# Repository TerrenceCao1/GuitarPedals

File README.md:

# Digital Guitar Pedals

A modular digital guitar pedal platform built on the STM32F103C8T6 microcontroller. The goal is a single hardware enclosure that can be reflashed to produce different effects.

---

## Effects Firmware

| Effect | Status |
|---|---|
| Bypass (clean passthrough) | Software Tested |
| Boost | Planned |
| Overdrive / Distortion | Planned |
| Delay | Planned |
| Chorus | Planned |
| Reverb | Planned |
| Tremolo | Planned |
| Tuner | Planned |
| Looper | Planned |

---

## Hardware

### Signal Chain

```
Guitar → 1/4" input jack → input protection → op-amp buffer → ADC (PCM1802)
                                                                      ↓
Amp    ← 1/4" output jack ←   output cap    ← DAC (PCM5102A) ← STM32 via I2S
```

### Power

Powered via USB through the STM32 Blue Pill's onboard regulator. No external PSU needed.

| Rail | Source | Powers |
|---|---|---|
| 3.3V | Blue Pill `3V3` pin | STM32, PCM1802, PCM5102A |
| 5V | Blue Pill `5V` pin | MCP6002 op-amp |

### Components

| Component | Part | Status | Link |
|---|---|---|---|
| Microcontroller | STM32F103C8T6 (Blue Pill) | Have | — |
| ADC | PCM1802 | Ordered | [Amazon](https://www.amazon.com/PCM1808-Single-Ended-Analog-Input-Decoder-Amplifier/dp/B0D9LNGBD1) |
| DAC | PCM5102A breakout | Ordered | [Amazon](https://www.amazon.com/ACEIRMC-Lossless-Digital-Converter-Raspberry/dp/B08YNJGSN4) |
| Op-amp | MCP6002 (rail-to-rail, 3.3V/5V) | Ordered | [Amazon](https://www.amazon.com/MICROCHIP-MCP6002-I-OP-AMP-DIP-8-pieces/dp/B00LPJXQJW) |
| Input/output jacks | GLS 1/4" female panel jacks × 2 | Ordered | [Amazon](https://www.amazon.com/GLS-Audio-Jacks-Female-Panel/dp/B00CMXRLXM) |
| Input protection | 1MΩ resistor + 10nF capacitor | Ordered | [Resistors](https://www.amazon.com/ALLECIN-8W-Resistor-Film-Assortment/dp/B0BTP6WYH1) / [Caps](https://www.amazon.com/Multilayer-Monolithic-Capacitor-Assortment-Electronics/dp/B0D2GVNDHY) |
| Decoupling caps | 100nF ceramic × 8, 10µF electrolytic × 2 | Needed | — |
| Breadboard + jumper wires | Full-size 830-tie | Have | — |

---

## Roadmap

- [ ] Breadboard MVP — get audio passing through STM32 via I2S
- [ ] Implement and test simulations (pure software on computer)
- [ ] Test effects on firmware
- [ ] Wire potentiometers for live parameter control
- [ ] Design schematic and PCB
- [ ] Design and fabricate enclosure

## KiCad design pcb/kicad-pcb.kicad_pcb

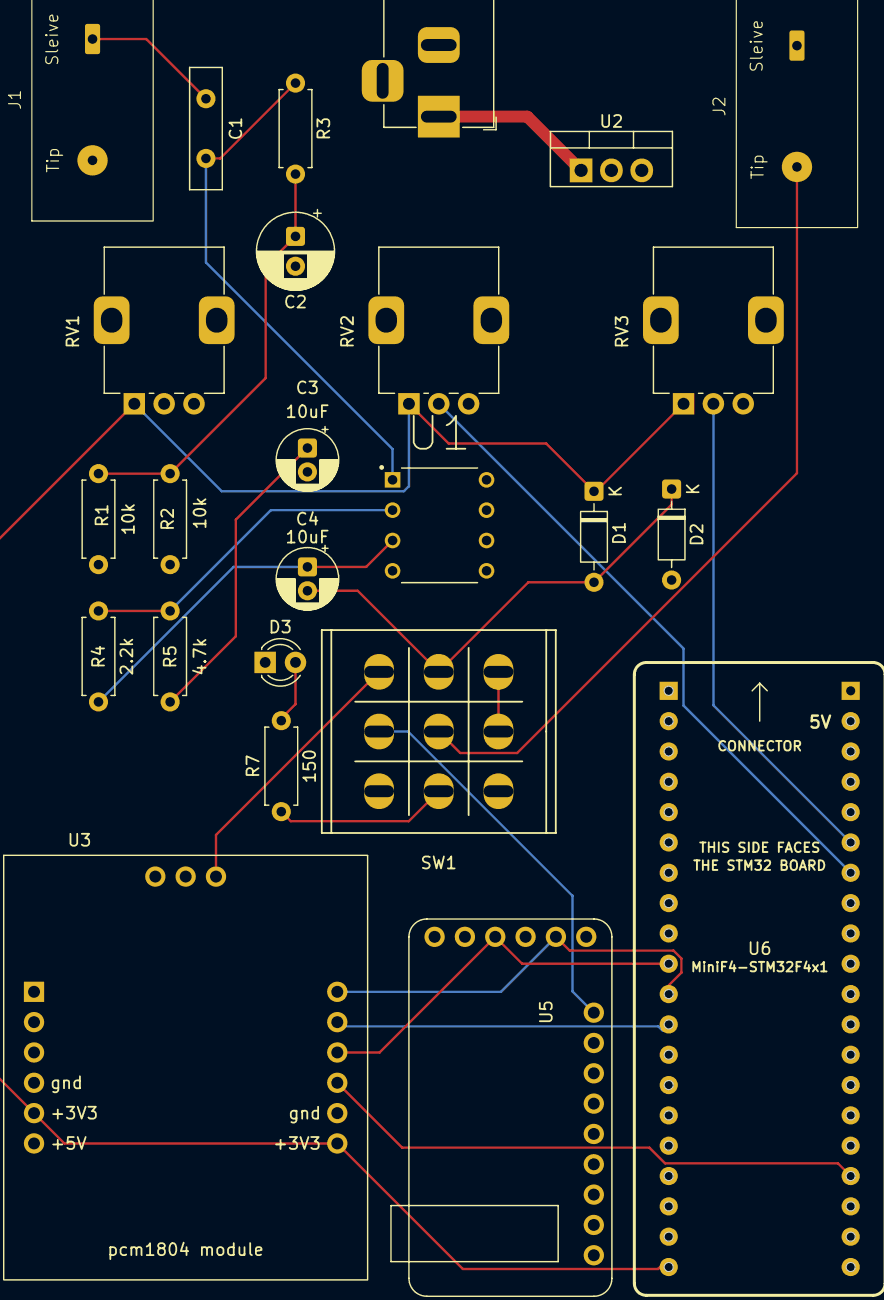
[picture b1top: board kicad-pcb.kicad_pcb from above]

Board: 4 copper layers, 25 parts (0 on the bottom side), 25 nets.

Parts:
C1: 0.1uF; C_Disc_D10.0mm_W2.5mm_P5.00mm
C2: 47uF; CP_Radial_D6.3mm_P2.50mm
C3, C4: 10uF; CP_Radial_D5.0mm_P2.00mm
D1, D2: BAT41; D_DO-35_SOD27_P7.62mm_Horizontal
D3: LED; LED_D3.0mm
J1: InputJack; AudioJack
J2: OutputJack; AudioJack
J3: Power Jack; BarrelJack_Horizontal
R1, R2: 10k; R_Axial_DIN0207_L6.3mm_D2.5mm_P7.62mm_Horizontal
R3: 1M; R_Axial_DIN0207_L6.3mm_D2.5mm_P7.62mm_Horizontal
R4: 2.2k; R_Axial_DIN0207_L6.3mm_D2.5mm_P7.62mm_Horizontal
R5: 4.7k; R_Axial_DIN0207_L6.3mm_D2.5mm_P7.62mm_Horizontal
R7: 150; R_Axial_DIN0207_L6.3mm_D2.5mm_P7.62mm_Horizontal
RV1: Knob1; Potentiometer_Alps_RK09K_Single_Vertical
RV2: Knob2; Potentiometer_Alps_RK09K_Single_Vertical
RV3: Knob3; Potentiometer_Alps_RK09K_Single_Vertical
SW1: Switches_Stomp_Switch_3PDT
U1: DIP787W46P254L927H533Q8
U2: LM7805_TO220; TO-220-3_Vertical
U3: pcm_adc
U5: GY-PCM5102
U6: Mini_F4X1_STM32

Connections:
+3.3V: D1.1 (K), RV1.1, RV2.1, RV3.1, U3.8 (3.3V), U3.15 (3.3V), U6.20 (3V3), U6.23 (3V3)
+5V: R1.1, SW1.7 (A), U1.4 (V+), U2.3 (VO), U3.9 (5V), U5.6 (VIN), U6.18 (5V), U6.21 (5V)
+9V: J3.1, U2.1 (VI)
GND: C2.2, C3.2, D2.2 (A), D3.1 (K), J1.T, J2.S, J3.2, R2.2, RV1.3, RV2.3, RV3.3, SW1.9 (C), U2.2 (GND), U3.2 (GND), U3.4 (FMT), U3.5 (MD1), U3.6 (MD0), U3.7 (GND), U3.14 (GND), U5.1 (SCK), U5.5 (GND), U5.12 (G), U5.14 (G), U6.19 (GND), U6.22 (GND)
unnamed: C1.1, J1.S
unnamed: C2.1, R1.2, R2.1, R3.2
unnamed: C3.1, R5.2
unnamed: C4.1, R4.1, U1.3
unnamed: C4.2, D1.2 (A), D2.1 (K), SW1.2 (B)
unnamed: D3.2 (A), R7.2
unnamed: SW1.1 (A), U3.3 (LIN)
unnamed: SW1.3 (C), SW1.6 (C)
unnamed: SW1.4 (A), U5.15 (L)
unnamed: J2.T, SW1.5 (B)
unnamed: R7.1, SW1.8 (B)
unnamed: C1.2, R3.1, U1.1 (+)
unnamed: R4.2, R5.1, U1.2 (-)
unnamed: U3.10 (BCK), U5.2 (BCK), U6.11 (B3)
unnamed: U3.12 (LRC), U5.4 (LCK), U6.10 (A15)
unnamed: U3.11 (OUT), U6.12 (B4)
unnamed: U3.13 (SCK), U6.24 (B10)
unnamed: U5.3 (DIN), U6.13 (B5)
unnamed: RV3.2, U6.35 (A0)
unnamed: RV2.2, U6.34 (A1)
unnamed: RV1.2, U6.32 (A3)

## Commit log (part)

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2026-06-03 initial commit, with AudioFrame data class
2026-06-03 added info/scope to the project
2026-06-08 reformatted tests and wrote distortion tests
2026-06-08 finished normalize and assignment operator for AudioFrame
2026-06-13 distort function tests
2026-06-13 readme updates
2026-06-20 cmake includes tests
2026-06-20 new access functions for obtaining data (to be manipulated)
2026-06-20 wrote obtaining data functions
2026-06-20 added bypass test
2026-06-20 Bypass effect complete!
2026-06-20 Bypass status updated
2026-06-21 added Boost + distortion + overdrive functions
2026-06-21 boost effect
2026-06-22 wrote boost test + cmake
2026-06-25 CMake for flashing!
2026-06-25 mainPedal.cpp
2026-06-25 wrote Bypass and Boost tests
2026-06-25 Driver stuff
2026-06-26 initialized the GPIO's, DMA, and I2S
2026-06-26 dma interrupt boilerplate
2026-06-26 converted AudioFrame data from using vectors to predetermined array sizes
2026-06-26 changed effects to take in arrays not vectors
